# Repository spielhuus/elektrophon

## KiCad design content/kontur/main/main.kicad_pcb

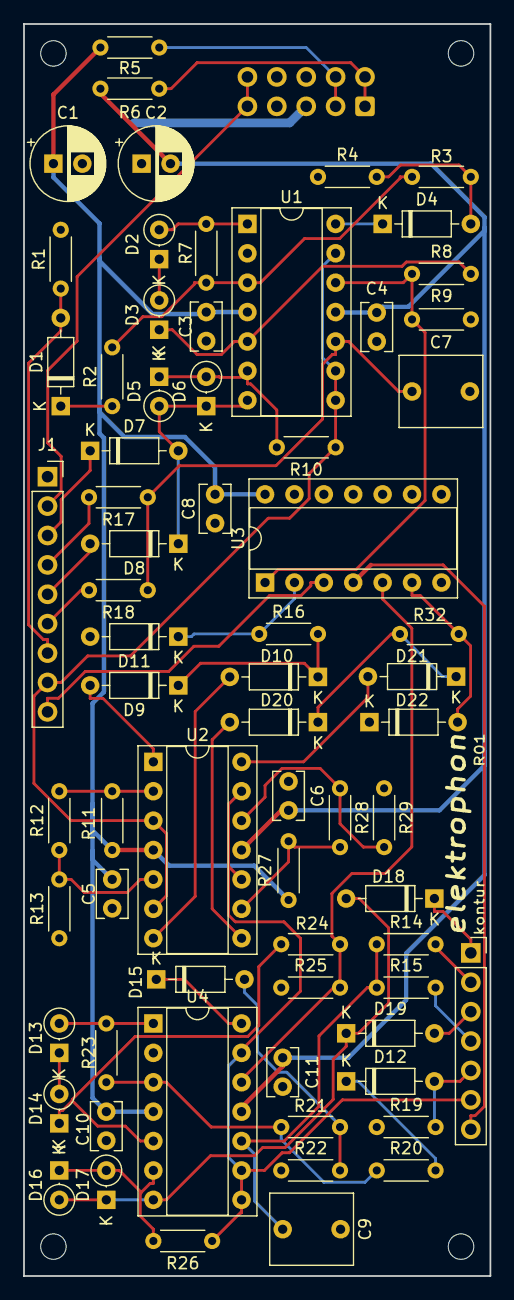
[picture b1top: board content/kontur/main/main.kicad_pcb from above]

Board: 2 copper layers, 40.3 x 108.2 mm, 74 parts (1 on the bottom side), 54 nets.

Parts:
C1, C2: 22u; CP_Radial_D6.3mm_P2.50mm
C3, C4, C5, C6, C8, C10, C11: 0.1u; C_Rect_L4.0mm_W2.5mm_P2.50mm
C7, C9: 4.7u; C_Rect_L7.0mm_W6.0mm_P5.00mm
D1, D4, D7, D8, D9, D10, D11, D12, D15, D18, D19, D20, D21, D22: 1N4148; D_DO-35_SOD27_P7.62mm_Horizontal
D2, D3, D5, D6, D13, D14, D16, D17: 1N4148; D_DO-35_SOD27_P2.54mm_Vertical_KathodeUp
H1, H2, H3, H4: MountingHole; MountingHole_2.2mm_M2
J1: 01x09 Female; PinSocket_1x09_P2.54mm_Vertical
J2: 10 Pos; IDC-Header_2x05_P2.54mm_Vertical
J3: 01x07 Female; PinSocket_1x07_P2.54mm_Vertical
R1, R16, R19, R32: 100k; R_Axial_DIN0204_L3.6mm_D1.6mm_P5.08mm_Horizontal
R2, R20: 27k; R_Axial_DIN0204_L3.6mm_D1.6mm_P5.08mm_Horizontal
R3, R21: 390k; R_Axial_DIN0204_L3.6mm_D1.6mm_P5.08mm_Horizontal
R4, R9, R22, R25: 47k; R_Axial_DIN0204_L3.6mm_D1.6mm_P5.08mm_Horizontal
R5, R6: 10; R_Axial_DIN0204_L3.6mm_D1.6mm_P5.08mm_Horizontal
R7, R23: 470k; R_Axial_DIN0204_L3.6mm_D1.6mm_P5.08mm_Horizontal
R8, R24: 2.2k; R_Axial_DIN0204_L3.6mm_D1.6mm_P5.08mm_Horizontal
R10, R26: 10k; R_Axial_DIN0204_L3.6mm_D1.6mm_P5.08mm_Horizontal
R11, R27: 36k; R_Axial_DIN0204_L3.6mm_D1.6mm_P5.08mm_Horizontal
R12, R14, R15, R17, R18, R28: 1k; R_Axial_DIN0204_L3.6mm_D1.6mm_P5.08mm_Horizontal
R13, R29: 220; R_Axial_DIN0204_L3.6mm_D1.6mm_P5.08mm_Horizontal
U1, U2, U4: LM324; DIP-14_W7.62mm_Socket
U3: 4001; DIP-14_W7.62mm_Socket

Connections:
+5V: J1.2, J2.9, J2.10
+15V: C1.1, C3.1, C5.1, C8.1, C10.1, R5.1, R11.2, R27.2, U1.4, U2.4, U3.14, U4.4
-15V: C2.2, C4.2, C6.2, C11.2, R6.1, U1.11, U2.11, U4.11
/sheet61728A8D/AA1: D7.1, J1.3
/sheet61728A8D/AA2: J1.4, R17.2
/sheet61728A8D/DA1: D8.2, J1.5
/sheet61728A8D/DA2: J1.6, R18.2
/sheet61728A8D/EOE1: J1.9, U3.3
/sheet61728A8D/IN1: D1.2, J1.7, R1.2
/sheet61728A8D/OUT1: J1.8, R10.1, U1.8, U1.9, U1.13, U2.3, U2.6
/sheet61729057/AB1: D18.1, J3.1
/sheet61729057/AB2: J3.2, R14.2
/sheet61729057/DB1: D19.2, J3.3
/sheet61729057/DB2: J3.4, R15.2
/sheet61729057/EOE2: J3.7, U3.4
/sheet61729057/IN2: D12.2, J3.5, R19.2
/sheet61729057/OUT2: J3.6, R26.1, U2.10, U2.13, U4.8, U4.9, U4.13
GND: C1.2, C2.1, C3.2, C4.1, C5.2, C6.1, C7.2, C8.2, C9.2, C10.2, C11.1, D11.2, D22.1, J1.1, J2.5, J2.6, J2.7, J2.8, R1.1, R4.1, R9.1, R13.1, R19.1, R22.1, R25.1, R29.1, U1.2, U3.7, U3.8, U3.9, U3.12, U3.13, U4.2
unnamed: C7.1, R17.1, R18.1, U1.10
unnamed: C9.1, R14.1, R15.1, U4.10
unnamed: D1.1, R2.2
unnamed: D2.1, D3.2
unnamed: D2.2, R7.1, U1.1
unnamed: D3.1, R8.2, U1.5
unnamed: D4.1, U1.14
unnamed: D4.2, R3.1, R4.2
unnamed: D5.1, D6.2, R10.2, U1.6
unnamed: D5.2, D6.1, D7.2, D8.1, U1.7
unnamed: D9.2, U2.1
unnamed: D9.1, D10.1, R16.2
unnamed: D10.2, U2.7
unnamed: D11.1, R16.1, U3.2
unnamed: D12.1, R20.2
unnamed: D13.1, D14.2
unnamed: D13.2, R23.1, U4.1
unnamed: D14.1, R24.2, U4.5
unnamed: D15.1, U4.14
unnamed: D15.2, R21.1, R22.2
unnamed: D16.1, D17.2, R26.2, U4.6
unnamed: D16.2, D17.1, D18.2, D19.1, U4.7
unnamed: D20.1, D21.1, R32.2
unnamed: D20.2, U2.8
unnamed: D21.2, U2.14
unnamed: D22.2, R32.1, U3.6
unnamed: R2.1, R3.2, R7.2, U1.3
unnamed: R8.1, R9.2, U1.12, U3.1
unnamed: R11.1, R12.2, U2.2
unnamed: R12.1, R13.2, U2.5
unnamed: R20.1, R21.2, R23.2, U4.3
unnamed: R24.1, R25.2, U3.5, U4.12
unnamed: R27.1, R28.2, U2.9
unnamed: R28.1, R29.2, U2.12
VN: J2.1, J2.2, R6.2
VP: J2.3, J2.4, R5.2

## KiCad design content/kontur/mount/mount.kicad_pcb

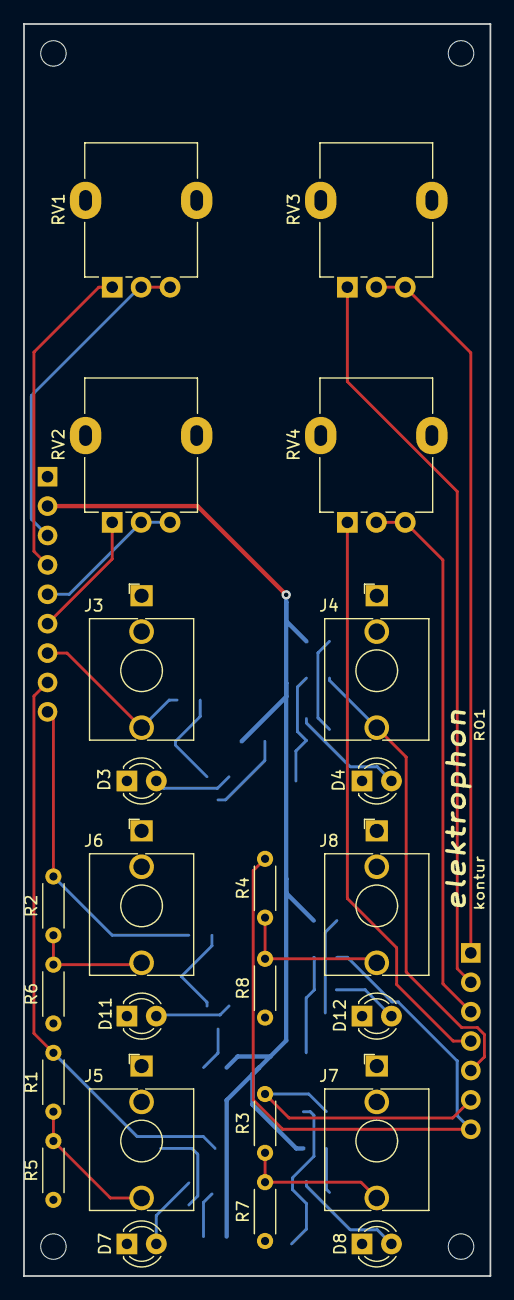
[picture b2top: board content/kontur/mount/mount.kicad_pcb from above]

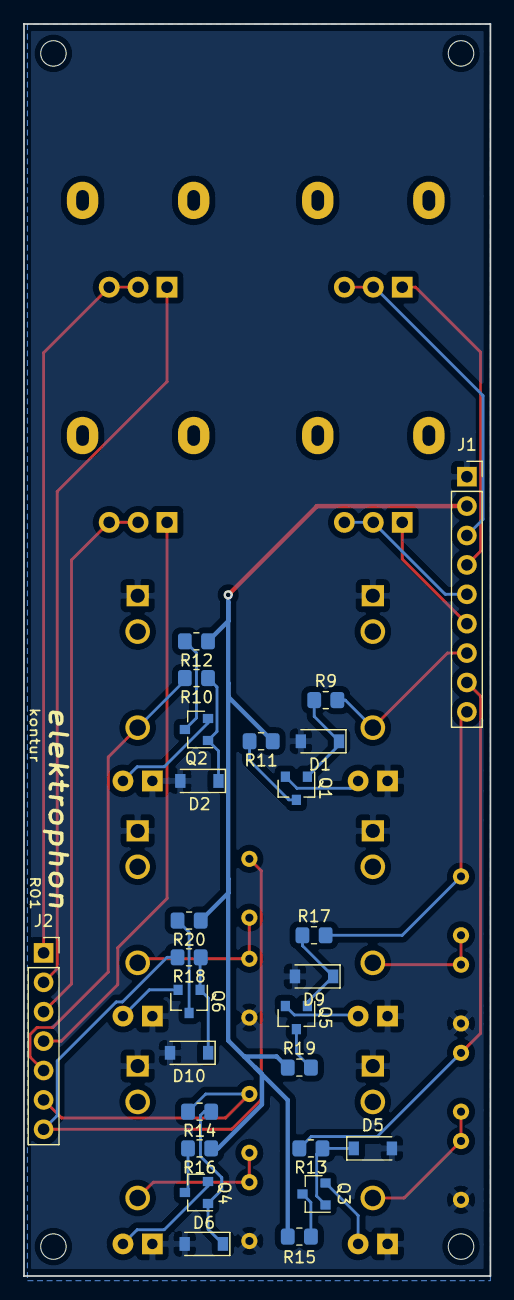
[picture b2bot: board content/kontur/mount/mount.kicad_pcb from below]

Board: 2 copper layers, 40.3 x 108.2 mm, 54 parts (26 on the bottom side), 38 nets.

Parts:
D1, D2, D5, D6, D9, D10: 1N4148W; D_SOD-123
D3, D4: LED (Yellow); LED_D3.0mm
D7, D8, D11, D12: LED (Red); LED_D3.0mm
H1, H2, H3, H4: MountingHole; MountingHole_2.2mm_M2
J1: 01x09 Male; PinSocket_1x09_P2.54mm_Vertical
J2: 01x07 Male; PinSocket_1x07_P2.54mm_Vertical
J3, J4, J5, J6, J7, J8: AudioJack2_SwitchT; Jack_3.5mm_WQP-PJ398SM_Vertical
Q1, Q2, Q3, Q4, Q5, Q6: MMBT3904; SOT-23
R1, R2, R3, R4, R5, R6, R7, R8: 2.2k; R_Axial_DIN0204_L3.6mm_D1.6mm_P5.08mm_Horizontal
R9, R10, R13, R14, R17, R18: 100k; R_0805_2012Metric_Pad1.20x1.40mm_HandSolder
R11, R12, R15, R16, R19, R20: 5.1k; R_0805_2012Metric_Pad1.20x1.40mm_HandSolder
RV1, RV3: 100k; Potentiometer_Alpha_RD901F-40-00D_Single_Vertical
RV2, RV4: 500k; Potentiometer_Alpha_RD901F-40-00D_Single_Vertical

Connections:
+5V: J1.2, R11.1, R12.1, R15.1, R16.1, R19.1, R20.1
/AA1: J1.3, RV1.2, RV1.3
/AA2: J1.4, RV1.1
/AB1: J2.1, RV3.2, RV3.3
/AB2: J2.2, RV3.1
/DA1: J1.5, RV2.2, RV2.3
/DA2: J1.6, RV2.1
/DB1: J2.3, RV4.2, RV4.3
/DB2: J2.4, RV4.1
/EOE1: J1.9, R2.2, R17.2
/EOE2: J2.7, R4.2, R18.2
/IN1: J1.7, J3.T, R9.2
/IN2: J2.5, J4.T, R10.2
/OUT1: J1.8, R1.2, R13.2
/OUT2: J2.6, R3.2, R14.2
GND: D1.2, D2.2, D3.1, D4.1, D5.2, D6.2, D7.1, D8.1, D9.2, D10.2, D11.1, D12.1, J1.1, J3.S, J4.S, J5.S, J6.S, J7.S, J8.S, R5.1, R6.1, R7.1, R8.1
unnamed: D1.1, Q1.1, R9.1
unnamed: D2.1, Q2.1, R10.1
unnamed: D3.2, Q1.2
unnamed: D4.2, Q2.2
unnamed: D5.1, Q3.1, R13.1
unnamed: D6.1, Q4.1, R14.1
unnamed: D7.2, Q3.2
unnamed: D8.2, Q4.2
unnamed: D9.1, Q5.1, R17.1
unnamed: D10.1, Q6.1, R18.1
unnamed: D11.2, Q5.2
unnamed: D12.2, Q6.2
unnamed: J5.T, R1.1, R5.2
unnamed: J6.T, R2.1, R6.2
unnamed: J7.T, R3.1, R7.2
unnamed: J8.T, R4.1, R8.2
unnamed: Q1.3, R11.2
unnamed: Q2.3, R12.2
unnamed: Q3.3, R15.2
unnamed: Q4.3, R16.2
unnamed: Q5.3, R19.2
unnamed: Q6.3, R20.2

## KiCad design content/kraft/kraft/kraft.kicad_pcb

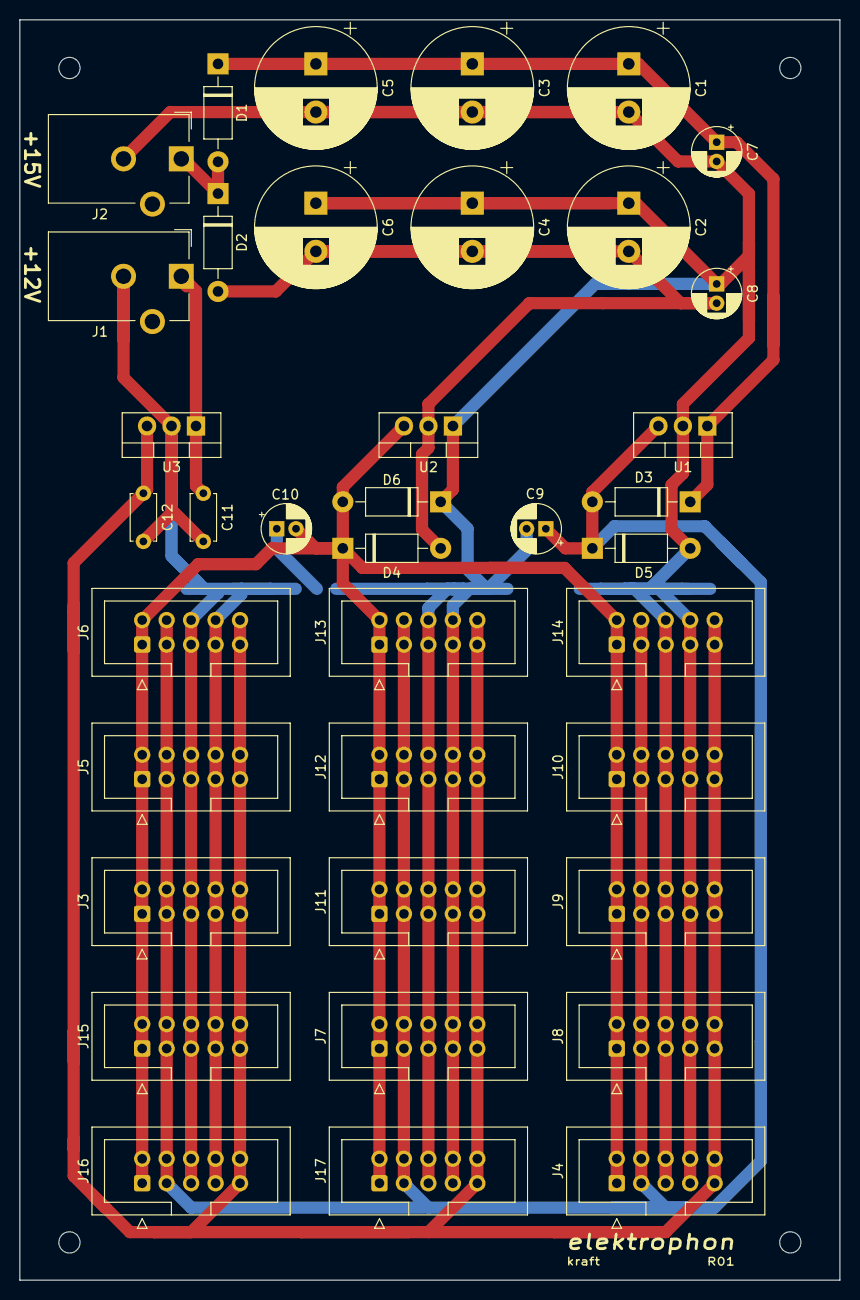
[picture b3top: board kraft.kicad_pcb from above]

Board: 2 copper layers, 85.1 x 130.8 mm, 42 parts (0 on the bottom side), 8 nets.

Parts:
C1, C2, C3, C4, C5, C6: 3300uF; CP_Radial_D12.5mm_P5.00mm
C7, C8, C9, C10: 1uF; CP_Radial_D5.0mm_P2.00mm
C11: 0.33; C_Disc_D4.7mm_W2.5mm_P5.00mm
C12: 0.1; C_Disc_D4.7mm_W2.5mm_P5.00mm
D1, D2, D3, D4, D5, D6: 1N4004; D_DO-41_SOD81_P10.16mm_Horizontal
H1, H2, H3, H4: MountingHole; MountingHole_2.2mm_M2
J1, J2: PJ-102AH; BarrelJack_CUI_PJ-102AH_Horizontal
J3, J4, J5, J6, J7, J8, J9, J10, J11, J12, J13, J14, J15, J16, J17: IDC Header; IDC-Header_2x05_P2.54mm_Vertical
U1: L7815; TO-220-3_Vertical
U2: L7915; TO-220-3_Vertical
U3: L7805; TO-220-3_Vertical

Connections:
15V_AC: D1.2, D2.1, J2.1
15V_N: C1.2, C2.1, C3.2, C4.1, C5.2, C6.1, C7.2, C8.1, C9.2, C10.1, C11.2, C12.2, D5.2, D6.1, J1.2, J2.2, J3.5, J3.6, J3.7, J3.8, J4.5, J4.6, J4.7, J4.8, J5.5, J5.6, J5.7, J5.8, J6.5, J6.6, J6.7, J6.8, J7.5, J7.6, J7.7, J7.8, J8.5, J8.6, J8.7, J8.8, J9.5, J9.6, J9.7, J9.8, J10.5, J10.6, J10.7, J10.8, J11.5, J11.6, J11.7, J11.8, J12.5, J12.6, J12.7, J12.8, J13.5, J13.6, J13.7, J13.8, J14.5, J14.6, J14.7, J14.8, J15.5, J15.6, J15.7, J15.8, J16.5, J16.6, J16.7, J16.8, J17.5, J17.6, J17.7, J17.8, U1.2, U2.1, U3.2
+5V: C12.1, J3.9, J3.10, J4.9, J4.10, J5.9, J5.10, J6.9, J6.10, J7.9, J7.10, J8.9, J8.10, J9.9, J9.10, J10.9, J10.10, J11.9, J11.10, J12.9, J12.10, J13.9, J13.10, J14.9, J14.10, J15.9, J15.10, J16.9, J16.10, J17.9, J17.10, U3.3
+12V: C11.1, J1.1, U3.1
+15V: C9.1, D3.2, D5.1, J3.3, J3.4, J4.3, J4.4, J5.3, J5.4, J6.3, J6.4, J7.3, J7.4, J8.3, J8.4, J9.3, J9.4, J10.3, J10.4, J11.3, J11.4, J12.3, J12.4, J13.3, J13.4, J14.3, J14.4, J15.3, J15.4, J16.3, J16.4, J17.3, J17.4, U1.3
-15V: C10.2, D4.1, D6.2, J3.1, J3.2, J4.1, J4.2, J5.1, J5.2, J6.1, J6.2, J7.1, J7.2, J8.1, J8.2, J9.1, J9.2, J10.1, J10.2, J11.1, J11.2, J12.1, J12.2, J13.1, J13.2, J14.1, J14.2, J15.1, J15.2, J16.1, J16.2, J17.1, J17.2, U2.3
unnamed: C1.1, C3.1, C5.1, C7.1, D1.1, D3.1, U1.1
unnamed: C2.2, C4.2, C6.2, C8.2, D2.2, D4.2, U2.2

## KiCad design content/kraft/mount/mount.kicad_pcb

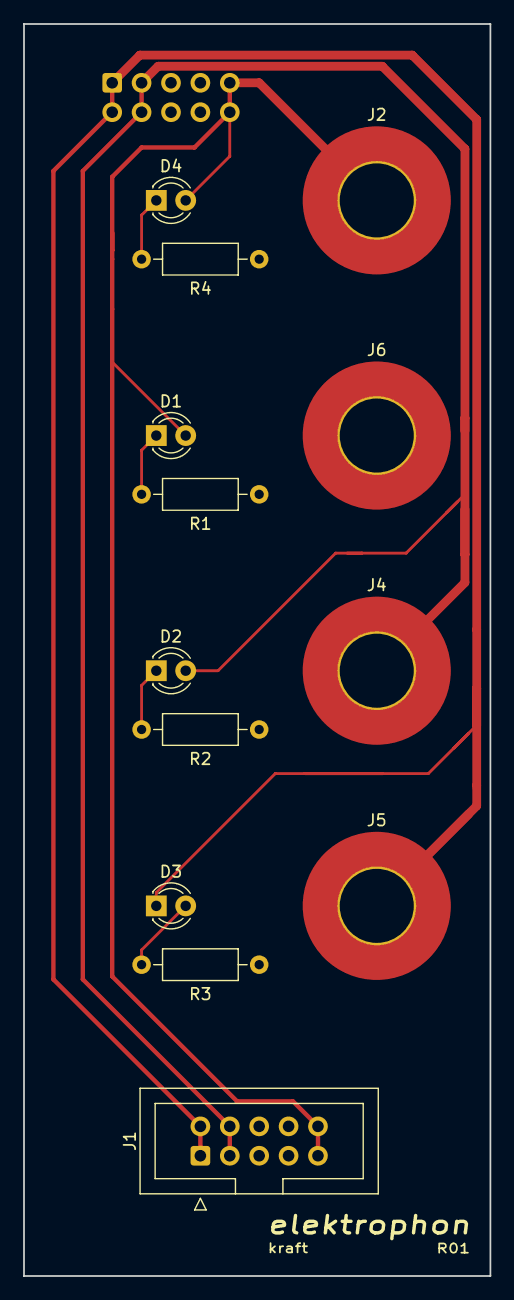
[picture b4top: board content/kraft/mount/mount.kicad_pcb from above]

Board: 2 copper layers, 40.3 x 108.2 mm, 14 parts (1 on the bottom side), 8 nets.

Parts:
D1, D2, D3, D4: LED; LED_D3.0mm
J1, J3: IDC Header; IDC-Header_2x05_P2.54mm_Vertical
J2, J4, J5, J6: CT2224; MountingHole_6.4mm_M6_Pad_TopBottom
R1: 1k2; R_Axial_DIN0207_L6.3mm_D2.5mm_P10.16mm_Horizontal
R2, R3: 6k8; R_Axial_DIN0207_L6.3mm_D2.5mm_P10.16mm_Horizontal
R4: 2k2; R_Axial_DIN0207_L6.3mm_D2.5mm_P10.16mm_Horizontal

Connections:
+5V: D1.2, D4.2, J1.9, J1.10, J2.1, J3.9, J3.10
+15V: D2.2, J1.3, J1.4, J3.3, J3.4, J4.1
-15V: D3.1, J1.1, J1.2, J3.1, J3.2, J5.1
GND: J1.5, J1.6, J1.7, J1.8, J3.5, J3.6, J3.7, J3.8, J6.1, R1.2, R2.2, R3.2, R4.2
unnamed: D1.1, R1.1
unnamed: D2.1, R2.1
unnamed: D3.2, R3.1
unnamed: D4.1, R4.1

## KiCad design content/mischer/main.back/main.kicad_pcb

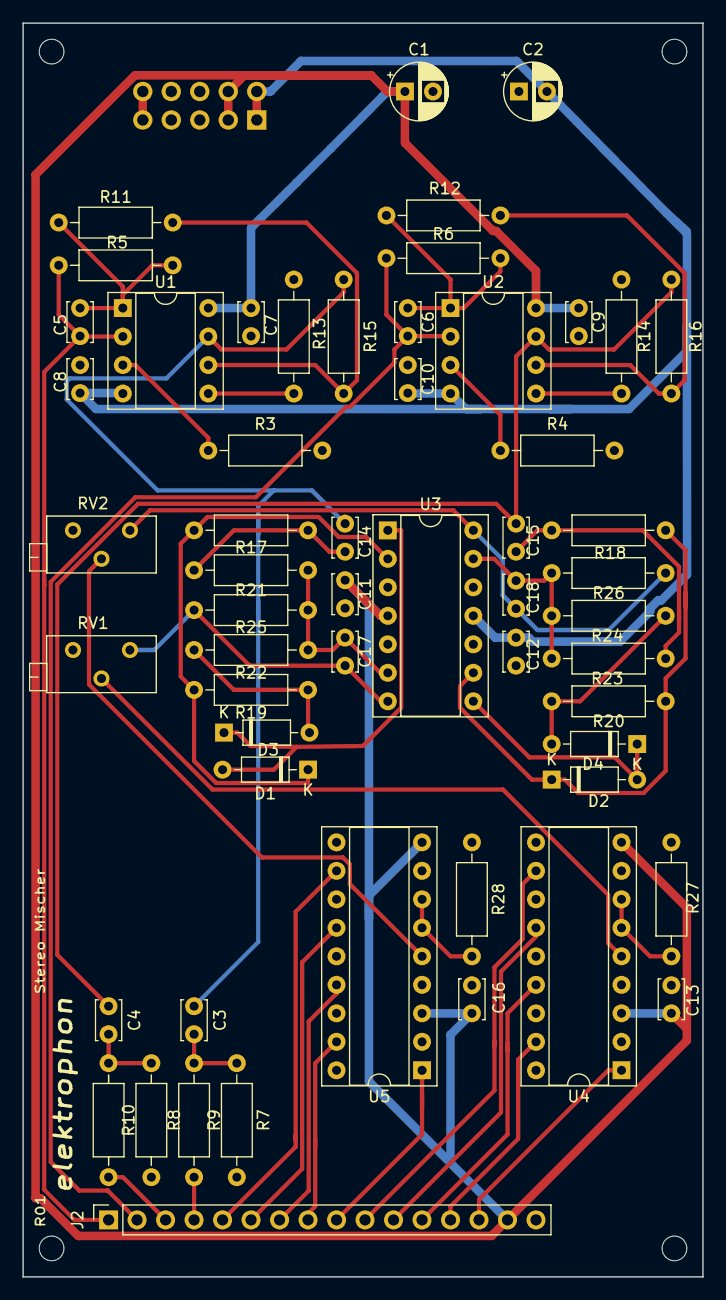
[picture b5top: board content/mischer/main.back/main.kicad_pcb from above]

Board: 2 copper layers, 60.6 x 111.8 mm, 57 parts (1 on the bottom side), 46 nets.

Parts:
C1, C2: 10u; CP_Radial_D5.0mm_P2.50mm
C3, C4: 4u7; C_Disc_D3.4mm_W2.1mm_P2.50mm
C5, C6: 47p; C_Disc_D3.4mm_W2.1mm_P2.50mm
C7, C8, C9, C10, C11, C12, C13, C16, C17, C18: 0.1u; C_Disc_D3.4mm_W2.1mm_P2.50mm
C14, C15: 0.47u; C_Disc_D3.4mm_W2.1mm_P2.50mm
D1, D2, D3, D4: 1N4148; D_DO-35_SOD27_P7.62mm_Horizontal
J1: IDC Header; IDC-Header_2x05_P2.54mm_Vertical
J2: Conn_01x16_Female; PinSocket_1x16_P2.54mm_Vertical
R3, R4, R7, R8, R13, R14: 5k; R_Axial_DIN0207_L6.3mm_D2.5mm_P10.16mm_Horizontal
R5, R6, R11, R12, R15, R16: 10k; R_Axial_DIN0207_L6.3mm_D2.5mm_P10.16mm_Horizontal
R9, R10: 1k; R_Axial_DIN0207_L6.3mm_D2.5mm_P10.16mm_Horizontal
R17, R18, R19, R20, R22, R24: 47k; R_Axial_DIN0207_L6.3mm_D2.5mm_P10.16mm_Horizontal
R21, R23, R25, R26: 100k; R_Axial_DIN0207_L6.3mm_D2.5mm_P10.16mm_Horizontal
R27, R28: 3k3; R_Axial_DIN0207_L6.3mm_D2.5mm_P10.16mm_Horizontal
RV1, RV2: 10k; Potentiometer_Bourns_3296Z_Horizontal
U1, U2: NE5532; DIP-8_W7.62mm_Socket
U3: TL074; DIP-14_W7.62mm_Socket
U4, U5: lm3916; DIP-18_W7.62mm_Socket

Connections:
+5V: J1.9, J1.10
+15V: C1.1, C7.1, C9.1, C11.1, C13.1, C16.1, J1.3, J1.4, J2.15, U1.8, U2.8, U3.4, U4.3, U4.9, U5.3, U5.9
-15V: C2.2, C8.2, C10.2, C12.2, J1.1, J1.2, U1.4, U2.4, U3.11
/LED_L_1: J2.14, U4.1
/LED_L_2: J2.13, U4.17
/LED_L_3: J2.12, U4.15
/LED_L_4: J2.11, U4.13
/LED_L_5: J2.10, U4.11
/LED_R_1: J2.9, U5.1
/LED_R_2: J2.8, U5.17
/LED_R_3: J2.7, U5.15
/LED_R_4: J2.6, U5.13
/LED_R_5: J2.5, U5.11
/LEFT: C5.2, J2.1, R5.2, U1.2
/LEFT_OUT: C3.1, C14.2, R15.1, U1.7
/RIGHT: C6.2, J2.2, R6.2, U2.2
/RIGHT_OUT: C4.1, C15.2, R16.1, U2.7
/STEREO_L: J2.4, R9.1
/STEREO_R: J2.3, R10.1
GND: C1.2, C2.1, C7.2, C8.1, C9.2, C10.1, C11.2, C12.1, C13.2, C16.2, J1.5, J1.6, J1.7, J1.8, J2.16, R3.2, R4.2, R7.2, R8.2, R13.2, R14.2, R27.1, R28.1, RV1.3, RV2.3, U3.3, U3.5, U3.10, U3.12, U4.2, U4.4, U4.8, U5.2, U5.4, U5.8
unnamed: C3.2, R7.1, R9.2
unnamed: C4.2, R8.1, R10.2
unnamed: C5.1, R5.1, R11.2, U1.1
unnamed: C6.1, R6.1, R12.2, U2.1
unnamed: C14.1, R17.2, R21.2
unnamed: C15.1, R18.2, R23.2
unnamed: C17.1, R25.1, RV1.1, U3.7
unnamed: C17.2, R21.1, R22.1, R25.2, U3.6
unnamed: C18.1, R26.1, RV2.1, U3.14
unnamed: C18.2, R23.1, R24.1, R26.2, U3.13
unnamed: D1.1, R17.1, R19.2, U3.2
unnamed: D1.2, D3.1, U3.1
unnamed: D2.1, R18.1, R20.2, U3.9
unnamed: D2.2, D4.1, U3.8
unnamed: D3.2, R19.1, R22.2
unnamed: D4.2, R20.1, R24.2
unnamed: R3.1, U1.3
unnamed: R4.1, U2.3
unnamed: R11.1, R15.2, U1.6
unnamed: R12.1, R16.2, U2.6
unnamed: R13.1, U1.5
unnamed: R14.1, U2.5
unnamed: R27.2, U4.6, U4.7
unnamed: R28.2, U5.6, U5.7
unnamed: RV1.2, U4.5
unnamed: RV2.2, U5.5

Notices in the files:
content/kontur/main/main.kicad_pcb:
License CC BY 4.0 - Attribution 4.0 International
